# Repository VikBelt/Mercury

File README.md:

# Mercury
Integrated Avionics Package for Rocket and UAV Needs

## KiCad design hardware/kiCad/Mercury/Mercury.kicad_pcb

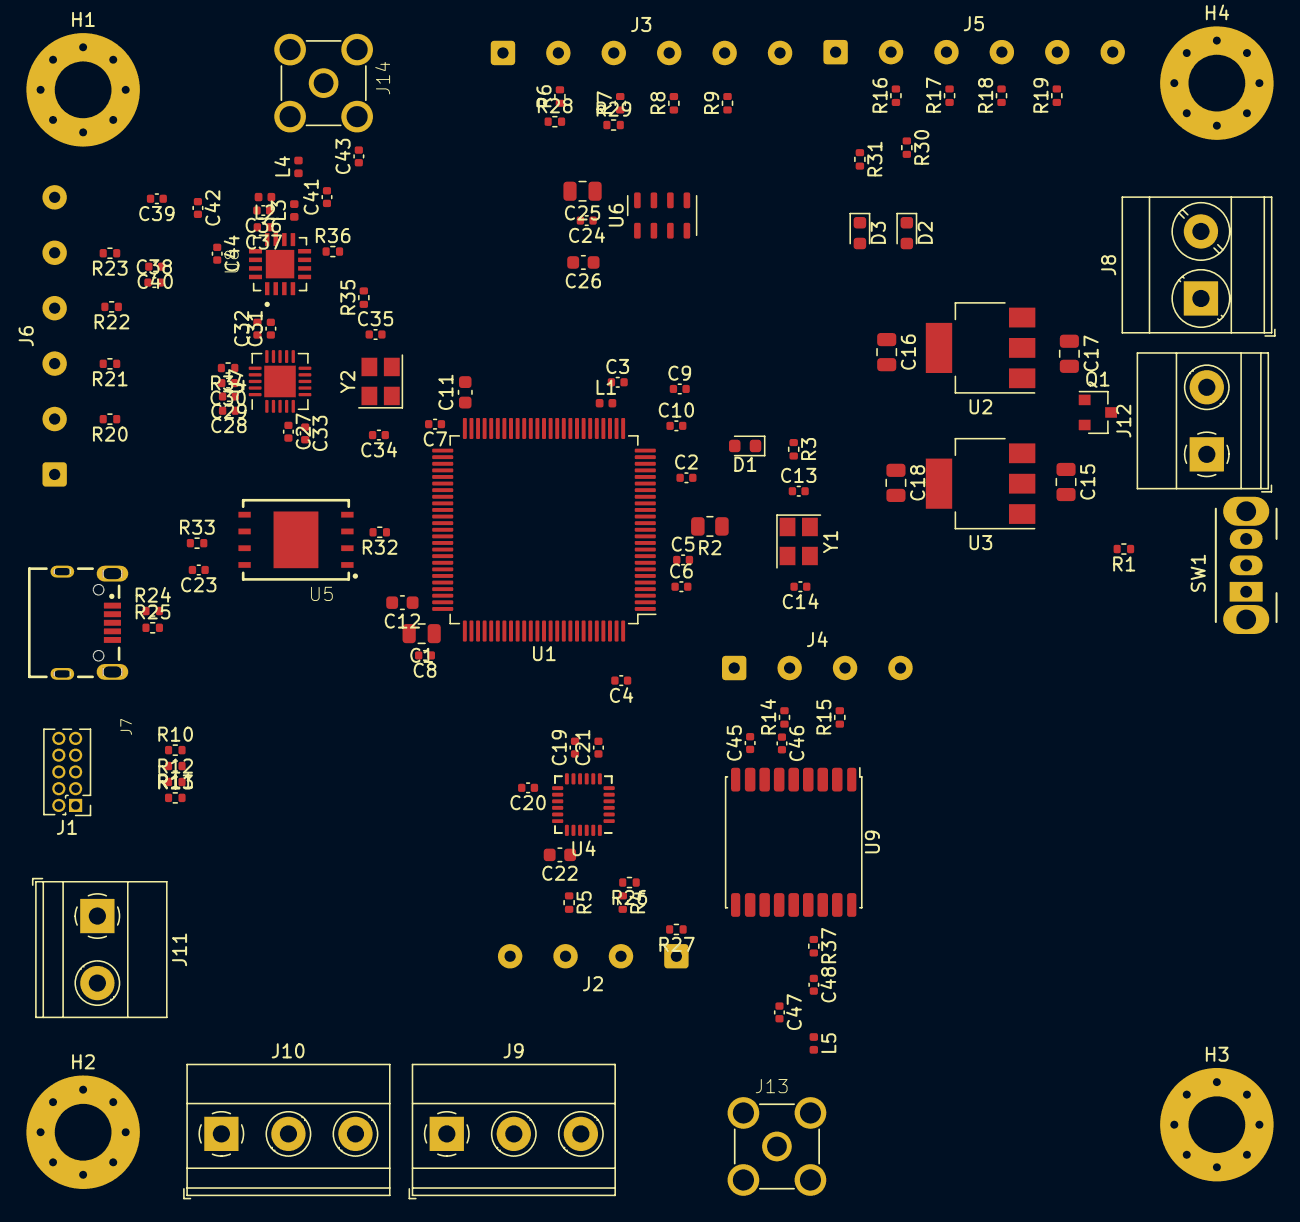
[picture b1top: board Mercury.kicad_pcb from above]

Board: 4 copper layers, 124 parts (0 on the bottom side), 103 nets, no tracks yet.

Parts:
C1: 4.7uF; C_0805_2012Metric
C2, C3, C4, C5, C6, C7, C8, C19, C20, C21, C23, C24, C27, C28, C29, C33: 100nF; C_0402_1005Metric
C9, C38, C45, C46: 1uF; C_0402_1005Metric
C10, C48: 10nF; C_0402_1005Metric
C11, C12: 2.2uF; C_0603_1608Metric
C13, C14, C34, C35, C40: 12pF; C_0402_1005Metric
C15, C16, C17, C18: 22uF; C_0805_2012Metric
C22: 2.2nF; C_0603_1608Metric
C25: 10uF; C_0805_2012Metric
C26: 100nF; C_0603_1608Metric
C30, C31, C32: 220pF; C_0402_1005Metric
C36: 1nF 0402; C_0402_1005Metric
C37: 12pF 0402; C_0402_1005Metric
C39: 1nF; C_0402_1005Metric
C41, C42: 2.2pF; C_0402_1005Metric
C43: 0.1pF; C_0402_1005Metric
C44: 18pF; C_0402_1005Metric
C47: 47pF; C_0402_1005Metric
D1: GREEN_LED; LED_0603_1608Metric
D2: RED_LED; LED_0603_1608Metric
D3: ORANGE_LED; LED_0603_1608Metric
H1, H2, H3, H4: MountingHole_Pad; MountingHole_4.3mm_M4_Pad_Via
J1: SWD; PinHeader_2x05_P1.27mm_Vertical
J2: I2C1; SolderWire-0.25sqmm_1x04_P4.2mm_D0.65mm_OD1.7mm
J3: I2C2; SolderWire-0.25sqmm_1x06_P4.2mm_D0.65mm_OD1.7mm
J4: UART1; SolderWire-0.25sqmm_1x04_P4.2mm_D0.65mm_OD1.7mm
J5: SPI1; SolderWire-0.25sqmm_1x06_P4.2mm_D0.65mm_OD1.7mm
J6: SPI2; SolderWire-0.25sqmm_1x06_P4.2mm_D0.65mm_OD1.7mm
J7: 629105150521
J8: Battery Input; TerminalBlock_Phoenix_MKDS-3-2-5.08_1x02_P5.08mm_Horizontal
J9: INPUT; TerminalBlock_Phoenix_MKDS-1,5-3-5.08_1x03_P5.08mm_Horizont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
J10: OUTPUT; TerminalBlock_Phoenix_MKDS-1,5-3-5.08_1x03_P5.08mm_Horizont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
J11: Analog I/O; TerminalBlock_Phoenix_MKDS-1,5-2-5.08_1x02_P5.08mm_Horizont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
J12: Power Rails; TerminalBlock_Phoenix_MKDS-1,5-2-5.08_1x02_P5.08mm_Horizont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
J13, J14: 5-1814832-1; TE_5-1814832-1
L1: 39nH; L_0402_1005Metric
L2: 4.7nH; L_0402_1005Metric
L3: 1nH; L_0402_1005Metric
L4: 1.8nH; L_0402_1005Metric
L5: 27nH; L_0402_1005Metric
Q1: AO3401A; SOT-23
R1: 10k; R_0402_1005Metric
R2: 47; R_0805_2012Metric
R3, R30: 1k; R_0402_1005Metric
R4, R5, R6, R7, R8, R9, R10, R11, R12, R13, R14, R15, R16, R17, R18, R19, R20, R21, R22, R23, R24, R25: 22; R_0402_1005Metric
R26, R27, R28, R29, R32, R33: 4k7; R_0402_1005Metric
R31: 4.7k; R_0402_1005Metric
R34: 56k; R_0402_1005Metric
R35: 47; R_0402_1005Metric
R36: 3.9k 0402; R_0402_1005Metric
R37: 10; R_0402_1005Metric
SW1: SW_SPDT; SW_CuK_OS102011MA1QN1_SPDT_Angled
U1: STM32F407VGT6; LQFP-100_14x14mm_P0.5mm
U2: AMS1117-3.3; SOT-223-3_TabPin2
U3: AMS1117-5.0; SOT-223-3_TabPin2
U4: MPU-6050; InvenSense_QFN-24_4x4mm_P0.5mm
U5: W25N01GVZEIG_TR; SON127P800X600X80-9N
U6: MPL3115A2; NXP_LGA-8_3x5mm_P1.25mm_H1.1mm
U7: CC2500; Texas_S-PVQFN-N20_EP2.4x2.4mm
U8: CC2592RGVR; QFN65P400X400X100-17N
U9: MAX-8Q; ublox_MAX
Y1: HSE 16MHz; Crystal_SMD_3225-4Pin_3.2x2.5mm
Y2: 26 MHz Oscillator; Crystal_SMD_3225-4Pin_3.2x2.5mm

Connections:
+3.3VA: C9.1, C10.1, L1.2, U1.22
+3V3: C1.1, C2.1, C3.1, C4.1, C5.1, C6.1, C7.1, C8.1, C16.1, C20.1, C21.1, C23.1, C25.1, C26.1, C27.1, C36.1, C37.1, C38.2, C39.2, C40.2, C45.1, C46.1, D2.2, J1.9, J2.1, J3.1, J4.1, J5.1, J6.1, J12.2, L1.1, L2.2, R26.1, R27.1, R28.1, R29.1, R32.1, R33.1, SW1.1, U1.6, U1.11, U1.19, U1.28, U1.50, U1.75, U1.100, U2.2, U4.8, U4.13, U5.8, U6.1, U6.4, U7.4, U7.9, U7.11, U7.14, U7.15, U7.18, U8.13, U8.14, U8.15, U9.6, U9.7, U9.8
+5V: C18.1, D3.2, J12.1, U3.2
AGPIO1: J11.1, U1.81
AGPIO2: J11.2, U1.80
ALT_INT_1: R9.1, U1.46, U6.6
ALT_INT_2: R8.1, U1.45, U6.5
BOOT0: R1.2, U1.94
FLASH_CS: R23.1, U1.51, U5.1
GND: C1.2, C2.2, C3.2, C4.2, C5.2, C6.2, C7.2, C8.2, C9.2, C10.2, C11.2, C12.2, C13.2, C14.2, C15.2, C16.2, C17.2, C18.2, C19.2, C20.2, C21.2, C22.2, C23.2, C24.2, C25.2, C26.2, C27.2, C28.2, C29.2, C30.2, C31.2, C32.2, C33.2, C34.2, C35.2, C38.1, C39.1, C40.1, C41.1, C42.1, C43.1, C45.2, C46.2, C48.2, H1.1, H2.1, H3.1, H4.1, J1.1, J1.5, J1.7, J2.4, J3.6, J4.4, J5.6, J6.6, J7.5, J8.2, J13.2, J13.3, J13.4, J13.5, J14.2, J14.3, J14.4, J14.5, Q1.1, R3.2, R30.2, R31.2, R34.2, R36.2, SW1.3, U1.10, U1.20, U1.27, U1.74, U1.99, U2.1, U3.1, U4.9, U4.18, U5.4, U6.3, U7.16, U7.19, U7.21, U8.1, U8.4, U8.9, U8.11, U8.12, U8.16, U9.1, U9.10, U9.12, Y1.2, Y1.4, Y2.2, Y2.4
GPS_LNA_EN: U1.65, U9.13
GPS_RF_IN: C47.1, U9.11
GPS_RF_VCC: R37.1, U9.14
HSE_OSC_IN: C13.1, U1.12, Y1.1
HSE_OSC_OUT: R2.2, U1.13
I2C1_SCL: R4.1, R26.2, U1.92, U4.23
I2C1_SDA: R5.1, R27.2, U1.93, U4.24
I2C2_SCL: R6.1, R28.2, U1.47, U6.8
I2C2_SDA: R7.1, R29.2, U1.48, U6.7
IMU_CAP_OUT: C22.1, U4.20
IMU_INT: U1.91, U4.12
IMU_REG_OUT: C19.1, U4.10
Input1: J9.3, U1.87
Input2: J9.2, U1.86
Input3: J9.1, U1.85
NRST: R13.2, U1.14
unnamed: C14.1, R2.1, Y1.3
unnamed: C28.1, C29.1, C30.1, C31.1, C32.1
unnamed: C33.1, U7.5
unnamed: C35.1, R35.2, Y2.3
unnamed: C36.2, C37.2
unnamed: C42.2, L3.2, L4.1
unnamed: C43.2, C44.2, L4.2
unnamed: C44.1, J14.1
unnamed: C47.2, L5.1
unnamed: C48.1, J13.1, L5.2, R37.2
unnamed: D1.1, R3.1
unnamed: D2.1, R30.1
unnamed: D3.1, R31.1
unnamed: J1.2, R13.1
unnamed: J1.6, R12.1
unnamed: J1.8, R11.1
unnamed: J1.10, R10.1
unnamed: J2.2, R4.2
unnamed: J2.3, R5.2
unnamed: J3.2, R6.2
unnamed: J3.3, R7.2
unnamed: J3.4, R8.2
unnamed: J3.5, R9.2
unnamed: J4.2, R14.2
unnamed: J4.3, R15.2
unnamed: J5.2, R16.2
unnamed: J5.3, R17.2
unnamed: J5.4, R18.2
unnamed: J5.5, R19.2
unnamed: J6.2, R20.2
unnamed: J6.3, R21.2
unnamed: J6.4, R22.2
unnamed: J6.5, R23.2
unnamed: J7.2, R24.2
unnamed: J7.3, R25.2
unnamed: J7.S1, J7.S2, J7.S3, J7.S4
unnamed: R1.1, SW1.2
unnamed: R34.1, U7.17
unnamed: R36.1, U8.8
Output1: J10.1, U1.82
Output2: J10.2, U1.83
Output3: J10.3, U1.84
RF_ANT: C41.2, L2.1, L3.1, U8.10
RF_CS: R19.1, U1.33, U7.7
RF_GPO0: U1.38, U7.6
RF_GPO1: U1.37, U7.3
RF_HGM: U1.34, U8.7
RF_LNA_EN: U1.35, U8.6
RF_N: U7.13, U8.2
RF_P: U7.12, U8.3
RF_PA_EN: U1.36, U8.5
SPI1_MISO: R17.1, U1.31, U7.2
SPI1_MOSI: R18.1, U1.32, U7.20
SPI1_SCK: R16.1, U1.30, U7.1
SPI2_MISO: R21.1, U1.53, U5.2
SPI2_MOSI: R22.1, U1.54, U5.5
SPI2_SCK: R20.1, U1.52, U5.6
STATUS_LED: D1.2, U1.25
SWCLK: R11.2, U1.76
SWDIO: R10.2, U1.72
SWO: R12.2, U1.89
TIME_PULSE: U1.66, U9.4
UART1_RX: R15.1, U1.24, U9.2
UART1_TX: R14.1, U1.23, U9.3
USB_D+: R25.1, U1.71
USB_D-: R24.1, U1.70
V+: J8.1, Q1.3
VCAP_1: C11.1, U1.49
VCAP_2: C12.1, U1.73
V_CAP_ALT: C24.1, U6.2
Vin: C15.1, C17.1, Q1.2, U2.3, U3.3
XSOC_Q1: C34.1, U7.8, Y2.1
XSOC_Q2: R35.1, U7.10
~GPS_RESET: U1.67, U9.9
~GPS_SAFEBOOT: U1.64, U9.18
~HOLD: R33.2, U5.7
~WP: R32.2, U5.3

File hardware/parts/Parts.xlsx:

Reference Designator | Value | Footprint | Part # (LCSC) | Unit Price | Function / Notes | Reference
C1 | 4.7u | 0805 | C1779 |  | Bulk Decoupling of STM32 | STM32F407 Datasheet 5.1.6
C2 | 100n | 0402 | C1525 |  | Bulk Decoupling of STM32 | STM32F407 Datasheet 5.1.6
C3 | 100n | 0402 | C1525 |  | Bulk Decoupling of STM32 | STM32F407 Datasheet 5.1.6
C4 | 100n | 0402 | C1525 |  | Bulk Decoupling of STM32 | STM32F407 Datasheet 5.1.6
C5 | 100n | 0402 | C1525 |  | Bulk Decoupling of STM32 | STM32F407 Datasheet 5.1.6
C6 | 100n | 0402 | C1525 |  | Bulk Decoupling of STM32 | STM32F407 Datasheet 5.1.6
C7 | 100n | 0402 | C1525 |  | Bulk Decoupling of STM32 | STM32F407 Datasheet 5.1.6
C8 | 100n | 0402 | C1525 |  | Bulk Decoupling of STM32 | STM32F407 Datasheet 5.1.6
C9 | 1u | 0402 | C52923 |  | VDDA Analog Filtering | LTSpice
C10 | 10n | 0402 | C15195 |  | VDDA Analog Filtering | LTSpice
C11 | 2.2u | 0603 | C23630 |  | Stabilization of main internal regulator | STM32F407 Datasheet 5.3.2
C12 | 2.2u | 0603 | C23630 |  | Stabilization of main internal regulator | STM32F407 Datasheet 5.3.2
C13 | 12p | 0402 | C1547 |  | Crystal Load Capacitance | HSE 16MHz Datasheet
C14 | 12p | 0402 | C1547 |  | Crystal Load Capacitance | HSE 16MHz Datasheet
C15 | 22u | 0805 | C45783 |  | Voltage Regulator I/O decoupling | AMS1117 Datasheet
C16 | 22u | 0805 | C45783 |  | Voltage Regulator I/O decoupling | AMS1117 Datasheet
C17 | 22u | 0805 | C45783 |  | Voltage Regulator I/O decoupling | AMS1117 Datasheet
C18 | 22u | 0805 | C45783 |  | Voltage Regulator I/O decoupling | AMS1117 Datasheet
C19 | 100n | 0402 | C1525 |  | IMU Decoupling | MPU-6050 Datasheet 7.3
C20 | 100n | 0402 | C1525 |  | IMU Decoupling | MPU-6050 Datasheet 7.3
C21 | 100n | 0402 | C1525 |  | Regulator Filter Capacitor | MPU-6050 Datasheet 7.3
C22 | 2.2n | 0603 | C1604 |  | Charge Pump Capacitor | MPU-6050 Datasheet 7.3
C23 | 100n | 0402 | C1525 |  | Decoupling capacitor | Estimate
C24 | 100n | 0402 | C1525 |  | Decoupling capacitor | MPL3115A2 Datasheet
C25 | 10u | 0805 | C15850 |  | Decoupling capacitor | MPL3115A2 Datasheet
C26 | 100n | 0402 | C1525 |  | Decoupling capacitor | MPL3115A2 Datasheet
C27 | 100n | 0402 | C1525 |  | Decoupling capacitor | CC2500 Reference Schematic
C28 | 100n | 0402 | C1525 |  | Decoupling capacitor | CC2500 Reference Schematic
C29 | 100n | 0402 | C1525 |  | Decoupling capacitor | CC2500 Reference Schematic
C30 | 220p | 0402 | C1530 |  | Decoupling capacitor | CC2500 Reference Schematic
C31 | 220p | 0402 | C1530 |  | Decoupling capacitor | CC2500 Reference Schematic
C32 | 220p | 0402 | C1530 |  | Decoupling capacitor | CC2500 Reference Schematic
C33 | 100n | 0402 | C1525 |  | Decoupling capacitor | CC2500 Reference Schematic
C34 | 12p | 0402 | C1547 |  | Crystal Load Capacitance | HSE 26MHz Datasheet
C35 | 12p | 0402 | C1547 |  | Crystal Load Capacitance | HSE 26MHz Datasheet
C36 | 1n | 0402 | C1523 |  | Decoupling capacitor | CC2592 Reference Design
C37 | 12p | 0402 | C1547 |  | Decoupling capacitor | CC2592 Reference Design
C38 | 1u | 0402 | C52923 |  | Decoupling capacitor | CC2592 Reference Design
C39 | 1n | 0402 | C1523 |  | Decoupling capacitor | CC2592 Reference Design
C40 | 12p | 0402 | C1547 |  | Decoupling capacitor | CC2592 Reference Design
C41 | 2.2p | 0402 | C1559 |  | Impedance matching | CC2592 Reference Design
C43 | 0.1p | 0402 | C161338 |  | Impedance matching | CC2592 Reference Design
C44 | 18p | 0402 | C1549 |  | DC block capacitor | CC2592 Reference Design
C45 | 1u | 0402 | C52923 |  | Decoupling capacitor | Max-8Q Reference Design
C46 | 1u | 0402 | C52923 |  | Decoupling capacitor | Max-8Q Reference Design
C47 | 47p | 0402 | C1567 |  | Antenna match | Max-8Q Reference Design
C48 | 10n | 0402 | C27147 |  | Antenna match | Max-8Q Reference Design
D1 | Green LED | 0603 | C72043 |  | Status LED | n/a
D2 | Red LED | 0603 | C2286 |  | 3.3V LED | n/a
D3 | Orange LED | 0603 | C375450 |  | 5v LED | n/a
J1 | SWD | -- | Digikey |  | SWD connector | n/a
J2 | Wire Connector | -- | n/a |  | n/a | n/a
J3 | Wire Connector | -- | n/a |  | n/a | n/a
J4 | Wire Connector | -- | n/a |  | n/a | n/a
J5 | Wire Connector | -- | n/a |  | n/a | n/a
J6 | Wire Connector | -- | n/a |  | n/a | n/a
J7 | 629105150521 | -- | Digikey |  | n/a | n/a
J8 | 1x2 screw terminal | -- | Digikey |  | Screw Terminal | n/a
J9 | 1x3 screw terminal | -- | Digikey |  | Screw Terminal | n/a
J10 | 1x3 screw terminal | -- | Digikey |  | Screw Terminal | n/a
J11 | 1x2 screw terminal | -- | Digikey |  | Screw Terminal | n/a
J12 | 1x2 screw terminal | -- | Digikey |  | Screw Terminal | n/a
L1 | 39n | 0402 | C26443 |  | VDDA Analog Filtering | n/a
L2 | 4.7n | 0402 | C13595 |  | Antenna match | CC2592 Reference Design
L3 | 1n | 0402 | C18222 |  | Antenna match | CC2592 Reference Design
L4 | 1.8n | 0402 | C18304 |  | Antenna match | CC2592 Reference Design
L5 | 27n | 0402 | C12100 |  | Antenna match | Max-8Q Reference Design
Q1 | PMOS | -- | C15127 |  | Reverse Polarity Protection | n/a
R1 | 10k | 0402 | C25744 |  | Pullup/Down | n/a
R2 | 47 | 0805 | C17714 |  | Crystal Feed Resistor | n/a
R3 | 1k | 0402 | C11702 |  | Current Limiting Resistor | n/a
R4 | 22 | 0402 | C25092 |  | Current Limiting Resistor | n/a
R5 | 22 | 0402 | C25092 |  | Current Limiting Resistor | n/a
R6 | 22 | 0402 | C25092 |  | Current Limiting Resistor | n/a
R7 | 22 | 0402 | C25092 |  | Current Limiting Resistor | n/a
R8 | 22 | 0402 | C25092 |  | Current Limiting Resistor | n/a
R9 | 22 | 0402 | C25092 |  | Current Limiting Resistor | n/a
R10 | 22 | 0402 | C25092 |  | Current Limiting Resistor | n/a
R11 | 22 | 0402 | C25092 |  | Current Limiting Resistor | n/a
R12 | 22 | 0402 | C25092 |  | Current Limiting Resistor | n/a
R13 | 22 | 0402 | C25092 |  | Current Limiting Resistor | n/a
R14 | 22 | 0402 | C25092 |  | Current Limiting Resistor | n/a
R15 | 22 | 0402 | C25092 |  | Current Limiting Resistor | n/a
R16 | 22 | 0402 | C25092 |  | Current Limiting Resistor | n/a
R17 | 22 | 0402 | C25092 |  | Current Limiting Resistor | n/a
R18 | 22 | 0402 | C25092 |  | Current Limiting Resistor | n/a
R19 | 22 | 0402 | C25092 |  | Current Limiting Resistor | n/a
R20 | 22 | 0402 | C25092 |  | Current Limiting Resistor | n/a
R21 | 22 | 0402 | C25092 |  | Current Limiting Resistor | n/a
R22 | 22 | 0402 | C25092 |  | Current Limiting Resistor | n/a
R23 | 22 | 0402 | C25092 |  | Current Limiting Resistor | n/a
R24 | 22 | 0402 | C25092 |  | Current Limiting Resistor | n/a
R25 | 22 | 0402 | C25092 |  | Current Limiting Resistor | n/a
R26 | 4k7 | 0402 | C25900 |  | Pullup | n/a
R27 | 4k7 | 0402 | C25900 |  | Pullup | n/a
R28 | 4k7 | 0402 | C25900 |  | Pullup | n/a
R29 | 4k7 | 0402 | C25900 |  | Pullup | n/a
R30 | 1k | 0402 | C11702 |  | Current Limiting Resistor | n/a
R31 | 4k7 | 0402 | C25900 |  | Pullup | n/a
R32 | 4k7 | 0402 | C25900 |  | Pullup | n/a
R33 | 4k7 | 0402 | C25900 |  | Pullup | n/a
R34 | 56k | 0402 | C25796 |  | Bias Resistor | CC2500 Reference Schematic
R35 | 47 | 0402 | C25118 |  | Crystal Feed Resistor | n/a
R36 | 3k9 | 0402 | C51721 |  | Bias Resistor | CC2592 Reference Design
R37 | 10 | 0402 | C25744 |  | Pullup | Max-8Q Reference Design
SW1 | SPDT | n/a | Digikey |  | Boot0 Switch | STM32 Reference
U1 | F407 | QFP-100 | C12345 |  | MCU | n/a
U2 | 3.3 | SOT-223 | C6186 |  | 3.3v | AMS1117 Datasheet
U3 | 5.0 | SOT-223 | C6187 |  | 5.0v | AMS1117 Datasheet
U4 | MPU-6050 | QFN-24 | C24112 |  | IMU | MPU-6050 Datasheet
U5 | Flash | WSON-8_EP_6.0x8.0x1.27P | C88868 |  |  | n/a
U6 | Altimeter | LGA-8 | Digikey |  | Altimeter | n/a | C54429
U7 | RF Transciever | QFN-20 | Digikey |  | Transciever | n/a | C57494
U8 | RF PA | QFN-16 | C53274 |  | RF amplifier | n/a
U9 | GPS reciever | SMD-18 | Digikey |  | GPS | n/a
Y1 | 16 MHz Oscillator | SMD_3225 | C13738 |  | HSE MCU | n/a
Y2 | 26 MHz Oscillator | SMD_3225 | C23425 |  | RF HSE | n/a
 |  |  |  |  |  | n/a

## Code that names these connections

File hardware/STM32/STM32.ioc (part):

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Mcu.Name=STM32F407V(E-G)Tx
Mcu.Package=LQFP100
Mcu.UserName=STM32F407VGTx
PA0-WKUP.Mode=Asynchronous
PA0-WKUP.Signal=UART4_TX
PA1.Mode=Asynchronous
PA1.Signal=UART4_RX
PA11.Mode=Device_Only
PA11.Signal=USB_OTG_FS_DM
PA12.Mode=Device_Only
PA12.Signal=USB_OTG_FS_DP
PA13.Mode=Trace_Asynchronous_SW
PA13.Signal=SYS_JTMS-SWDIO
PA14.Mode=Trace_Asynchronous_SW
PA14.Signal=SYS_JTCK-SWCLK
PA2.Signal=GPIO_Output
PA5.Mode=Full_Duplex_Master
PA5.Signal=SPI1_SCK
PA6.Mode=Full_Duplex_Master
PA6.Signal=SPI1_MISO
PA7.Mode=Full_Duplex_Master
PA7.Signal=SPI1_MOSI
PA8.GPIOParameters=GPIO_Label
PA8.GPIO_Label=GPS_RESET
PA8.Signal=GPIO_Output
PB0.GPIOParameters=GPIO_Label
PB0.GPIO_Label=RF_LNA_EN
PB0.Signal=GPIO_Output
PB1.GPIOParameters=GPIO_Label
PB1.GPIO_Label=RF_PA_EN
PB1.Signal=GPIO_Output
PB10.Mode=I2C
PB10.Signal=I2C2_SCL
PB11.Mode=I2C
PB11.Signal=I2C2_SDA
PB12.GPIOParameters=GPIO_Label
PB12.GPIO_Label=FLASH_CS
PB12.Signal=GPIO_Output
PB13.Mode=Full_Duplex_Master
PB13.Signal=SPI2_SCK
PB14.Mode=Full_Duplex_Master
PB14.Signal=SPI2_MISO
PB15.Mode=Full_Duplex_Master
PB15.Signal=SPI2_MOSI
PB2.GPIOParameters=GPIO_Label
PB2.GPIO_Label=RF_GPO1
PB2.Signal=GPIO_Input
PB3.Mode=Trace_Asynchronous_SW
PB3.Signal=SYS_JTDO-SWO
PB5.GPIOParameters=GPIO_Label
PB5.GPIO_Label=IMU_INT
PB5.Signal=GPIO_Input
PB6.Mode=I2C
PB6.Signal=I2C1_SCL
PB7.Mode=I2C
PB7.Signal=I2C1_SDA
PC12.GPIOParameters=GPIO_Label
PC12.GPIO_Label=AGPIO2
PC12.Signal=GPIO_Analog
PC4.GPIOParameters=GPIO_Label
PC4.GPIO_Label=RF_CS
PC4.Signal=GPIO_Output
PC5.GPIOParameters=GPIO_Label
PC5.GPIO_Label=RF_HGM
PC5.Signal=GPIO_Output
PC7.GPIOParameters=GPIO_Label
PC7.GPIO_Label=GPS_SAFEBOOT
PC7.Signal=GPIO_Output
PC8.GPIOParameters=GPIO_Label
PC8.GPIO_Label=LNA_EN
PC8.Signal=GPIO_Output
PC9.GPIOParameters=GPIO_Label
PC9.GPIO_Label=TIME_PULSE
PC9.Signal=GPIO_Input
PD0.GPIOParameters=GPIO_Label
PD0.GPIO_Label=AGPIO1
PD0.Signal=GPIO_Analog
PD1.GPIOParameters=GPIO_Label
PD1.GPIO_Label=Output3
PD1.Signal=GPIO_Output
PD2.GPIOParameters=GPIO_Label
PD2.GPIO_Label=Output2
PD2.Signal=GPIO_Output
PD3.GPIOParameters=GPIO_Label
PD3.GPIO_Label=Output1
PD3.Signal=GPIO_Output
PD4.GPIOParameters=GPIO_Label
PD4.GPIO_Label=Input3
PD4.Signal=GPIO_Input
PD5.GPIOParameters=GPIO_Label
PD5.GPIO_Label=Input2
PD5.Signal=GPIO_Input
PD6.GPIOParameters=GPIO_Label
PD6.GPIO_Label=Input1
PD6.Signal=GPIO_Input
PE14.GPIOParameters=GPIO_Label
PE14.GPIO_Label=ALT_INT_2
PE14.Signal=GPIO_Output
PE15.GPIOParameters=GPIO_Label
PE15.GPIO_Label=ALT_INT_1
PE15.Signal=GPIO_Output
PE7.GPIOParameters=GPIO_Label
PE7.GPIO_Label=RF_GPO0
PE7.Signal=GPIO_Input
PH0-OSC_IN.Mode=HSE-External-Oscillator
PH0-OSC_IN.Signal=RCC_OSC_IN
PH1-OSC_OUT.Mode=HSE-External-Oscillator
PH1-OSC_OUT.Signal=RCC_OSC_OUT
RCC.HSE_VALUE=25000000
RCC.SYSCLKFreq_VALUE=16000000
board=custom

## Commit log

2020-12-19 Added Parts File
2020-12-21 More Parts
2020-12-22 Circuit_Started
2020-12-23 VDDA
2020-12-24 Clock
2020-12-24 Added Connectors
2020-12-25 USB CONNECTOR MICROB
2020-12-26 Peripherals Added
2020-12-26 GPS MODULE ADDED
2020-12-27 Schematic (Minus Connectors) Complete
2021-01-01 Footprints Assigned, Schematic Finalized
2021-01-02 Layout Begins
2021-01-04 prices
